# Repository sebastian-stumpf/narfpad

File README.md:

# narfpad

## BOM

- narfpad PCB
- 1 [Seed Studio XIAO RP2040](https://www.seeedstudio.com/XIAO-RP2040-v1-0-p-5026.html) (and sockets for it, optional but recommended)
- 10 SOD123 diodes
- 9 Kailh Choc Hotswap Sockets
- 9 Choc Switches (and keycaps)
- EC11 Encoder

## Hardware

The PCB has 5 mounting holes which allow for external mounting. Alternatively, there is a `tilter.stl`
from which you can generate a tilted case that snugly fits the PCB.

## Firmware

Firmware available at https://github.com/sebastian-stumpf/qmk_firmware/tree/sepp/keyboards/narfpad

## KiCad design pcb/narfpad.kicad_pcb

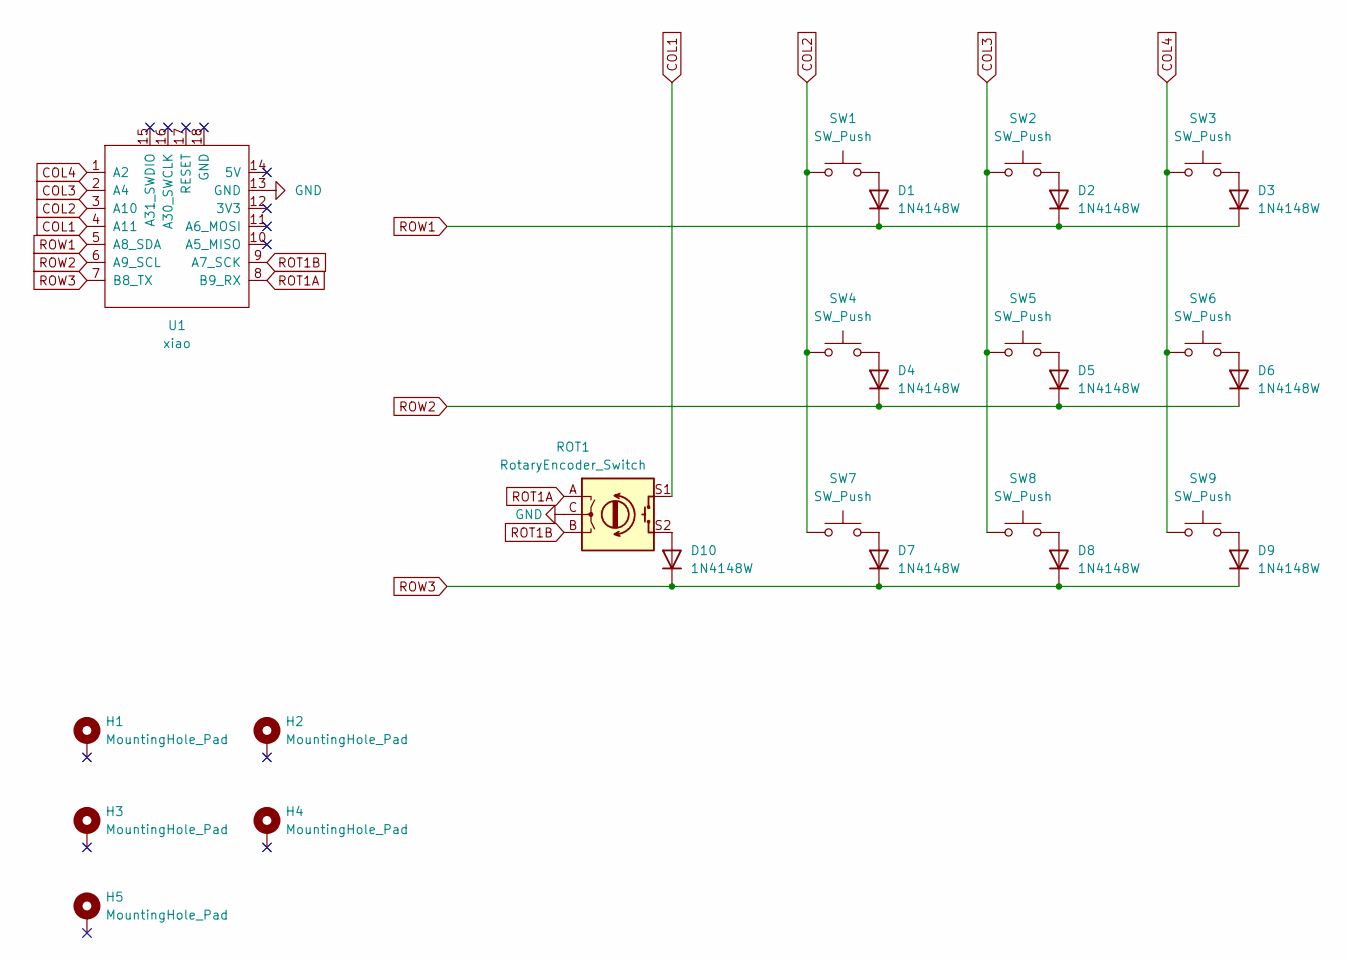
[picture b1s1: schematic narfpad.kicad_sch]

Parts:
D1, D2, D3, D4, D5, D6, D7, D8, D9, D10: 1N4148W; D_SOD-123
H1, H2, H3, H4, H5: MountingHole_Pad; MountingHole_2.2mm_M2_DIN965_Pad
ROT1: RotaryEncoder_Switch; RotaryEncoder_EC11
SW1, SW2, SW3, SW4, SW5, SW6, SW7, SW8, SW9: SW_Push; pg1350-H
U1: xiao; xiao-tht

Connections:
COL1: ROT1.S1, U1.4 (A11)
COL2: SW1.1, SW4.1, SW7.1, U1.3 (A10)
COL3: SW2.1, SW5.1, SW8.1, U1.2 (A4)
COL4: SW3.1, SW6.1, SW9.1, U1.1 (A2)
GND: ROT1.C, U1.13 (GND)
unnamed: D1.2 (A), SW1.2
unnamed: D2.2 (A), SW2.2
unnamed: D3.2 (A), SW3.2
unnamed: D4.2 (A), SW4.2
unnamed: D5.2 (A), SW5.2
unnamed: D6.2 (A), SW6.2
unnamed: D7.2 (A), SW7.2
unnamed: D8.2 (A), SW8.2
unnamed: D9.2 (A), SW9.2
unnamed: D10.2 (A), ROT1.S2
ROT1A: ROT1.A, U1.8 (B9_RX)
ROT1B: ROT1.B, U1.9 (A7_SCK)
ROW1: D1.1 (K), D2.1 (K), D3.1 (K), U1.5 (A8_SDA)
ROW2: D4.1 (K), D5.1 (K), D6.1 (K), U1.6 (A9_SCL)
ROW3: D7.1 (K), D8.1 (K), D9.1 (K), D10.1 (K), U1.7 (B8_TX)

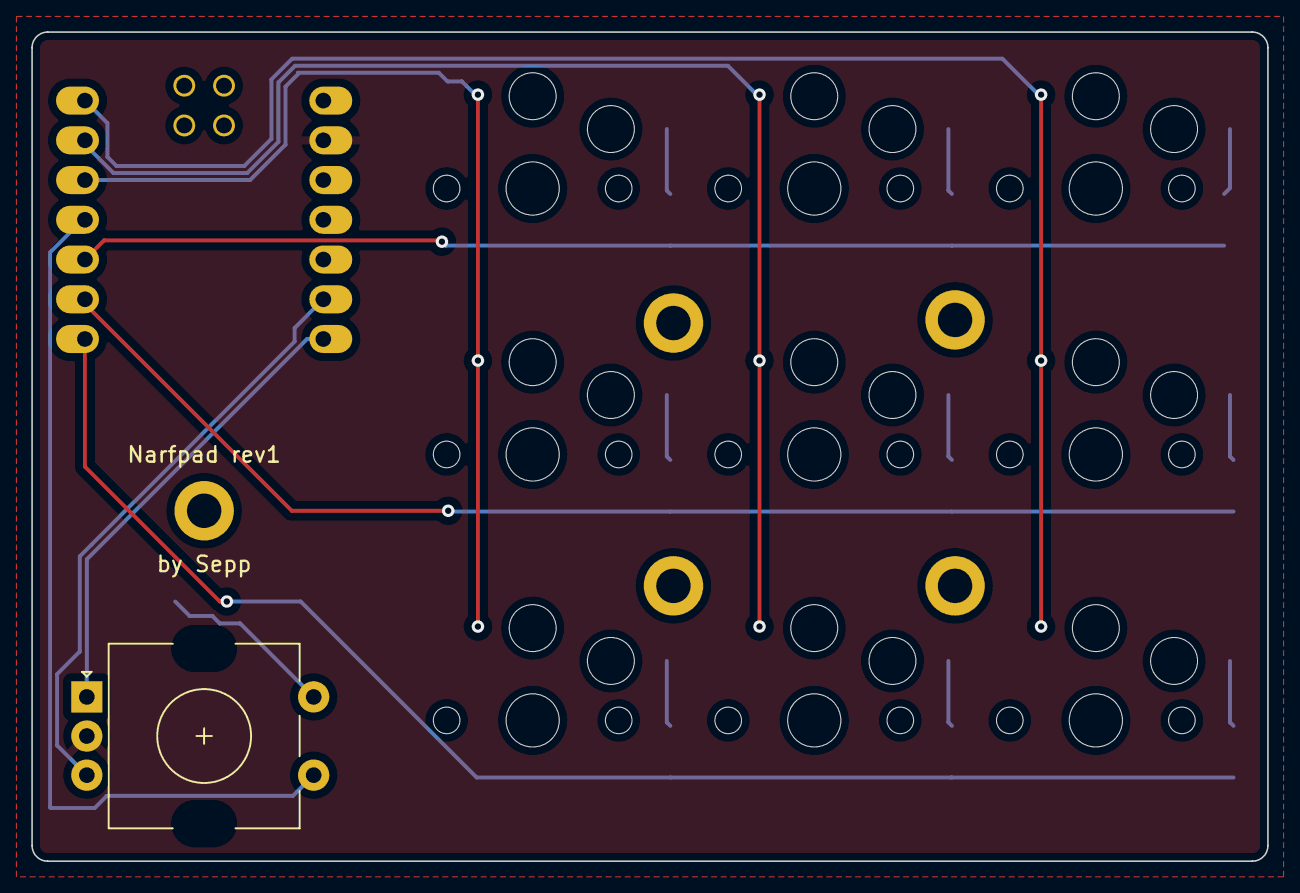
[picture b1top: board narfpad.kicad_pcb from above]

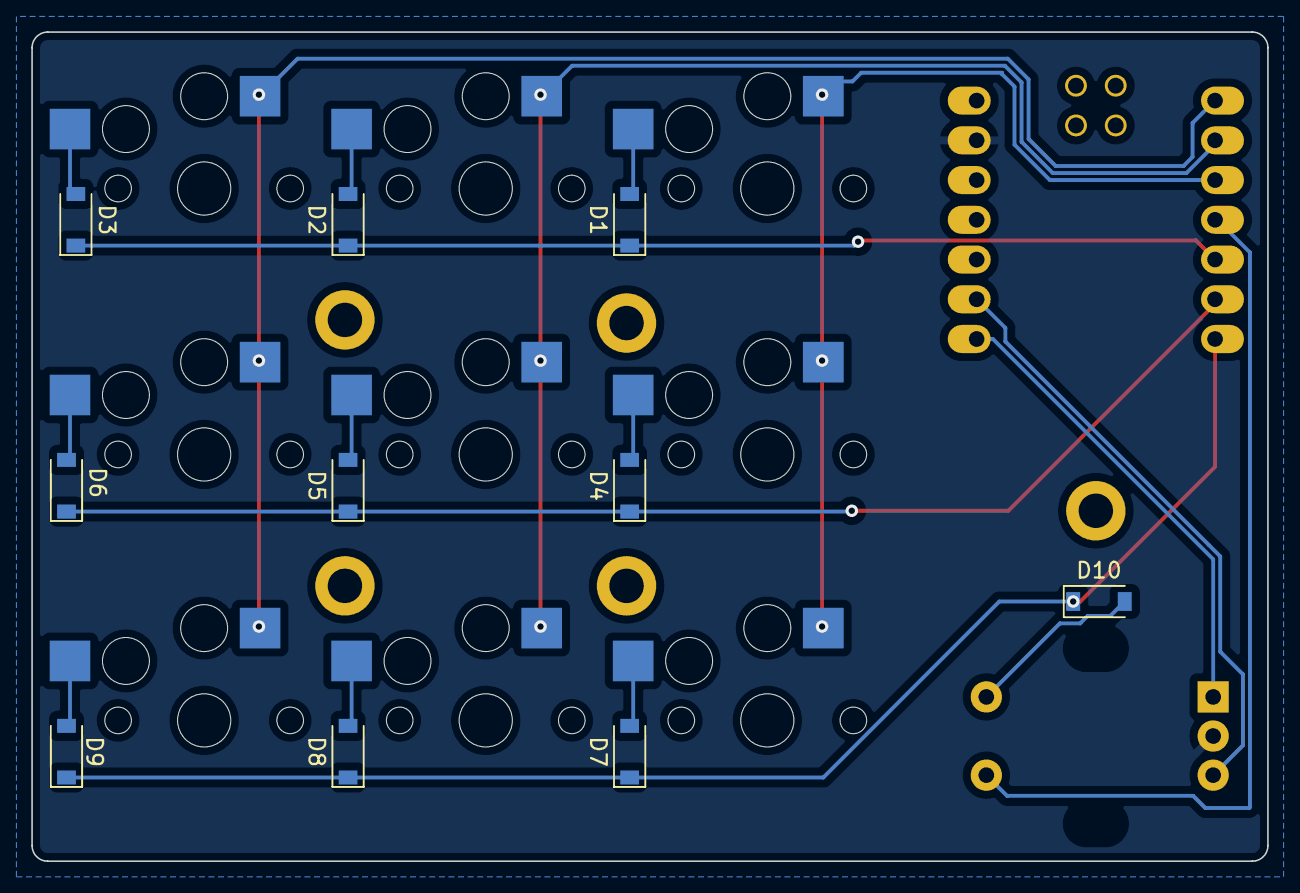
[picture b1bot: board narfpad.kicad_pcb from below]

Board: 2 copper layers, 79.0 x 53.0 mm, 26 parts (10 on the bottom side), 20 nets.

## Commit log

2023-03-08 added case picture
2024-11-13 Update README.md
    Adding hyperlinks for people who want to explore more
